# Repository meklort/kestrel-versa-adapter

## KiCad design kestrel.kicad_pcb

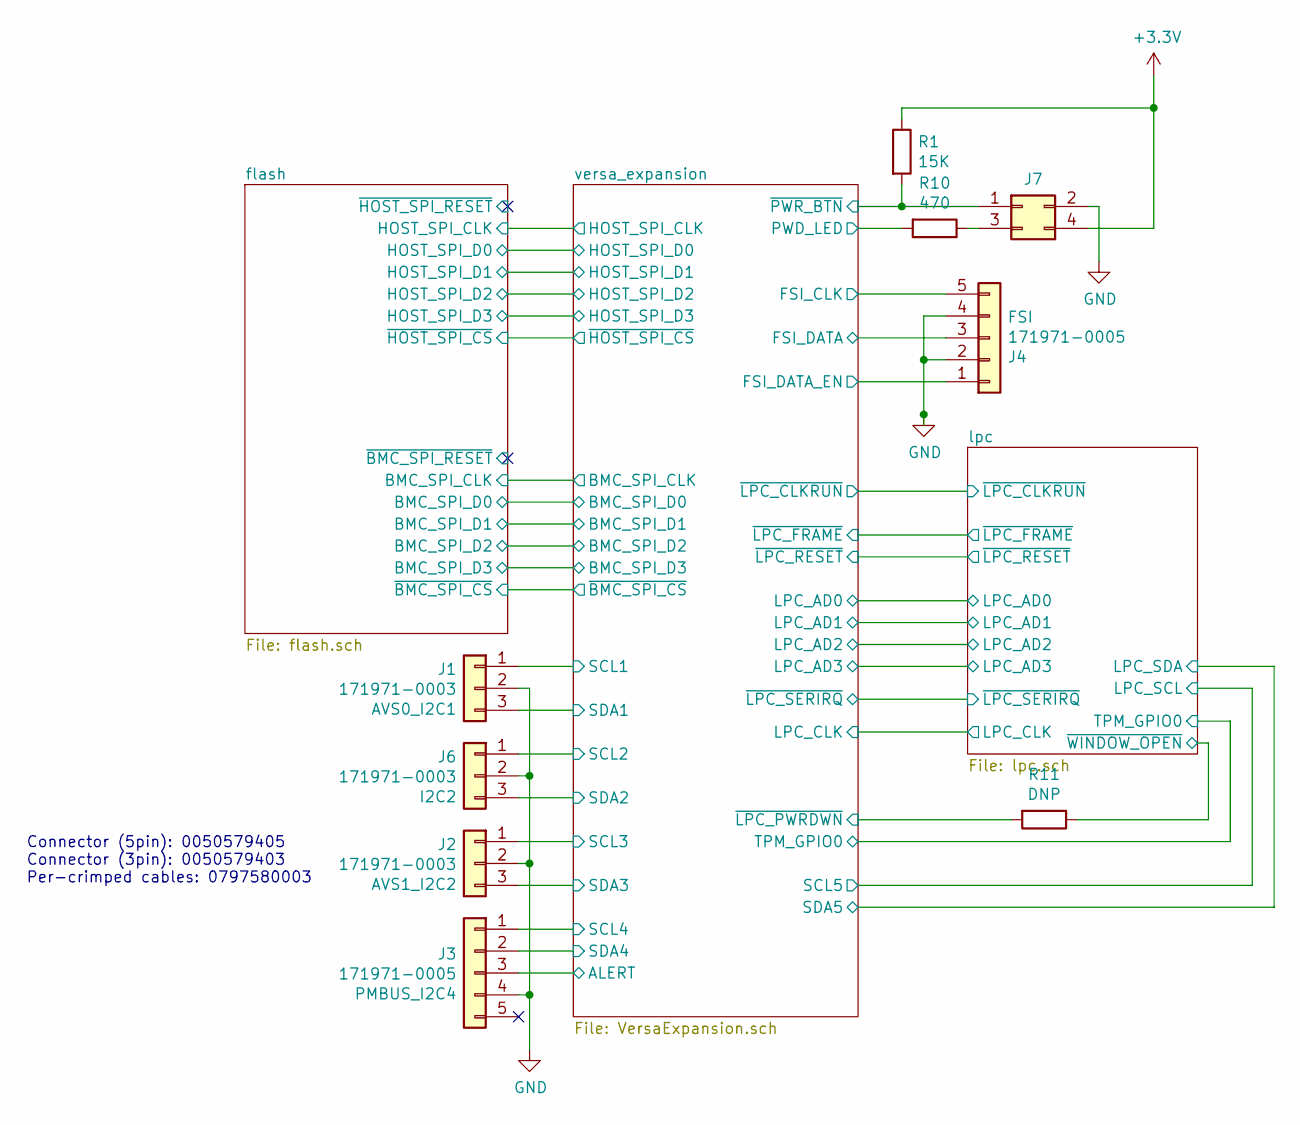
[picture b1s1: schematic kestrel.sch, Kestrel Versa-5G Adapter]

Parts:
J1, J2, J6: 171971-0003; Molex_SL_171971-0003_1x03_P2.54mm_Vertical
J3, J4: 171971-0005; Molex_SL_171971-0005_1x05_P2.54mm_Vertical
J7: Conn_02x02_Odd_Even; PinHeader_2x02_P2.54mm_Vertical
R1: 15K; R_0603_1608Metric_Pad0.98x0.95mm_HandSolder
R10: 470; R_0603_1608Metric_Pad0.98x0.95mm_HandSolder
R11: DNP; R_0603_1608Metric_Pad0.98x0.95mm_HandSolder

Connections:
+3V3: J7.4, R1.1; also elsewhere on the board
/lpc/~WINDOW_OPEN~: R11.1; also elsewhere on the board
/versa_expansion/ALERT: J3.3; also elsewhere on the board
/versa_expansion/FSI_CLK: J4.5; also elsewhere on the board
/versa_expansion/FSI_DATA: J4.3; also elsewhere on the board
/versa_expansion/FSI_DATA_EN: J4.1; also elsewhere on the board
/versa_expansion/PWD_LED: R10.2; also elsewhere on the board
/versa_expansion/SCL1: J1.1; also elsewhere on the board
/versa_expansion/SCL2: J6.1; also elsewhere on the board
/versa_expansion/SCL3: J2.1; also elsewhere on the board
/versa_expansion/SCL4: J3.1; also elsewhere on the board
/versa_expansion/SDA1: J1.3; also elsewhere on the board
/versa_expansion/SDA2: J6.3; also elsewhere on the board
/versa_expansion/SDA3: J2.3; also elsewhere on the board
/versa_expansion/SDA4: J3.2; also elsewhere on the board
/versa_expansion/~LPC_PWRDWN~: R11.2; also elsewhere on the board
/versa_expansion/~PWR_BTN~: J7.1, R1.2; also elsewhere on the board
GND: J1.2, J2.2, J3.4, J4.2, J4.4, J6.2, J7.2; also elsewhere on the board
unnamed: J7.3, R10.1

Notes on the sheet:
Connector (5pin): 0050579405 Connector (3pin): 0050579403 Per-crimped cables: 0797580003

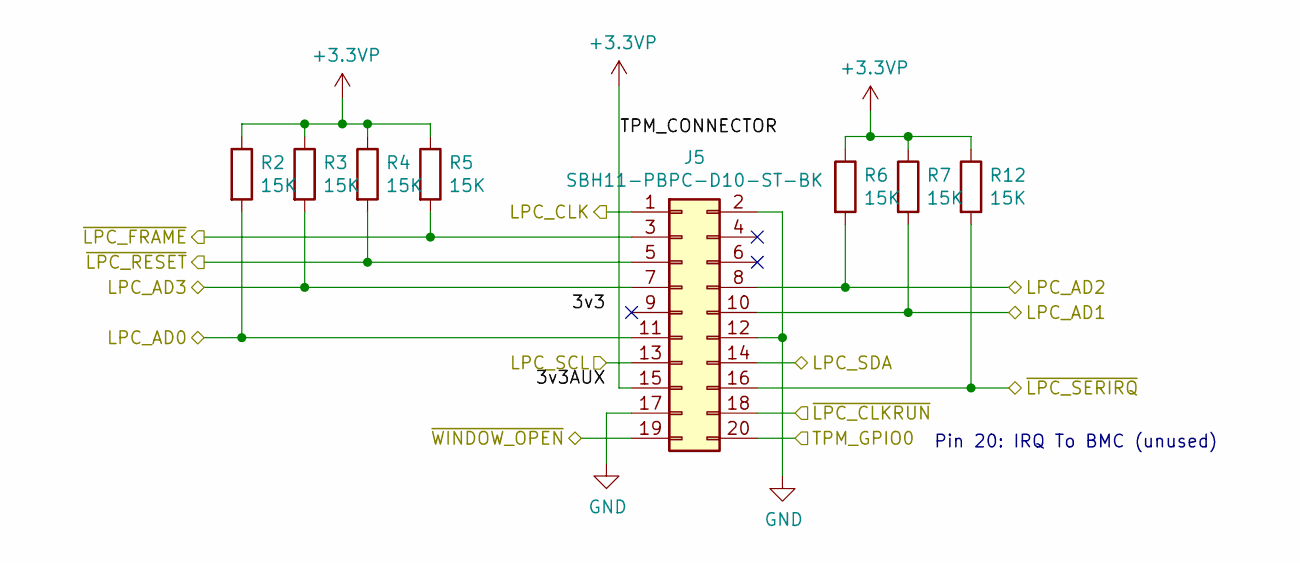
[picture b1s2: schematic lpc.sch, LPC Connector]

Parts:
J5: SBH11-PBPC-D10-ST-BK; PinHeader_2x10_P2.54mm_Vertical
R2, R3, R4, R5, R6, R7, R12: 15K; R_0603_1608Metric_Pad0.98x0.95mm_HandSolder

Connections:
+3.3VP: J5.15, R2.1, R3.1, R4.1, R5.1, R6.1, R7.1, R12.1
/lpc/LPC_AD0: J5.11, R2.2; also elsewhere on the board
/lpc/LPC_AD1: J5.10, R7.2; also elsewhere on the board
/lpc/LPC_AD2: J5.8, R6.2; also elsewhere on the board
/lpc/LPC_AD3: J5.7, R3.2; also elsewhere on the board
/lpc/LPC_CLK: J5.1; also elsewhere on the board
/lpc/LPC_SCL: J5.13; also elsewhere on the board
/lpc/LPC_SDA: J5.14; also elsewhere on the board
/lpc/TPM_GPIO0: J5.20; also elsewhere on the board
/lpc/~LPC_CLKRUN~: J5.18; also elsewhere on the board
/lpc/~LPC_FRAME~: J5.3, R5.2; also elsewhere on the board
/lpc/~LPC_RESET~: J5.5, R4.2; also elsewhere on the board
/lpc/~LPC_SERIRQ~: J5.16, R12.2; also elsewhere on the board
/lpc/~WINDOW_OPEN~: J5.19; also elsewhere on the board
GND: J5.2, J5.12, J5.17; also elsewhere on the board

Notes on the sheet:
Pin 20: IRQ To BMC (unused)

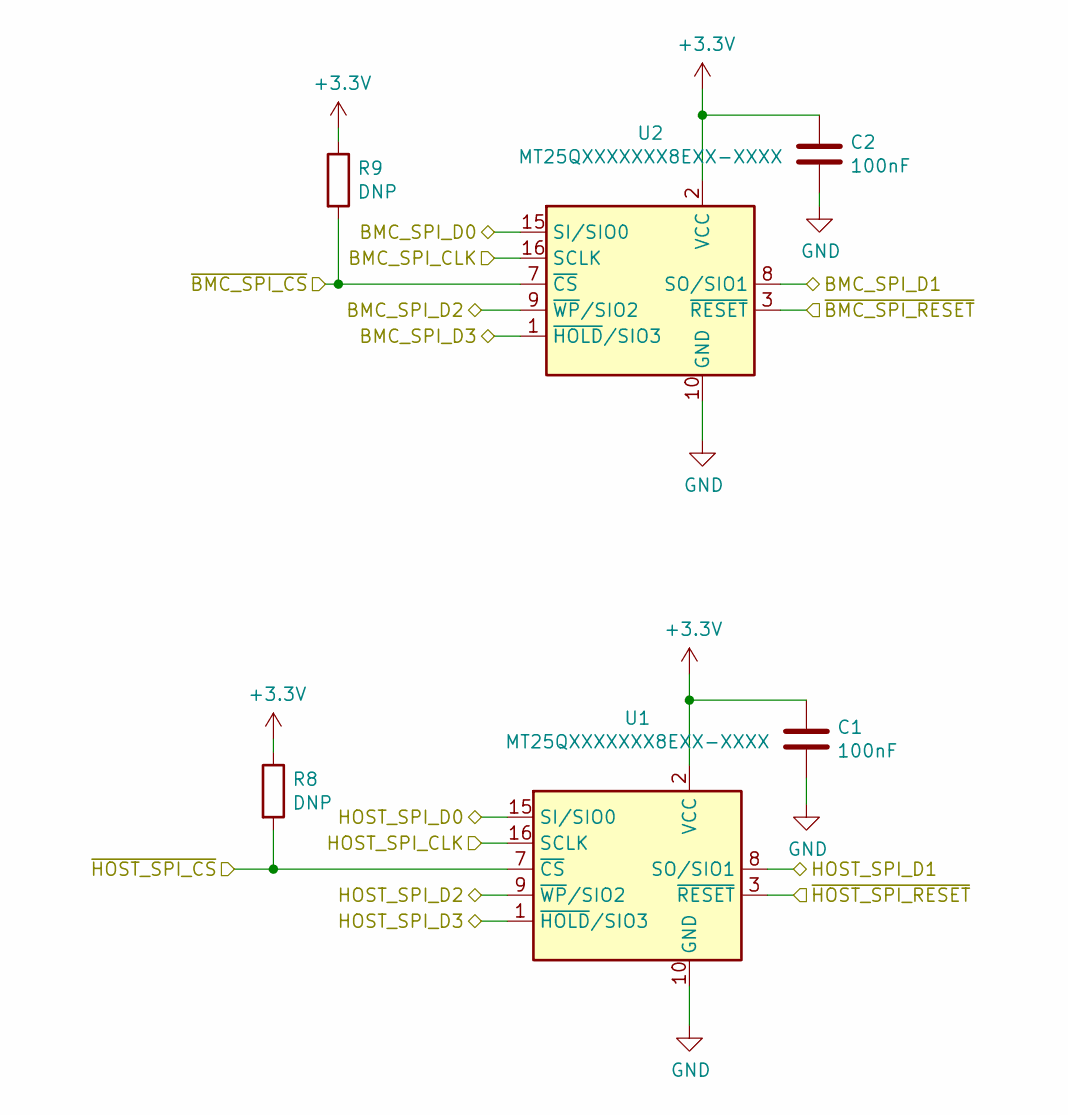
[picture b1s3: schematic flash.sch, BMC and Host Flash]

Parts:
C1, C2: 100nF; C_0603_1608Metric_Pad1.08x0.95mm_HandSolder
R8, R9: DNP; R_0603_1608Metric_Pad0.98x0.95mm_HandSolder
U1, U2: MT25QXXXXXXX8EXX-XXXX; SOIC-16W_7.5x10.3mm_P1.27mm

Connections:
+3V3: C1.1, C2.1, R8.1, R9.1, U1.2 (VCC), U2.2 (VCC); also elsewhere on the board
/flash/BMC_SPI_CLK: U2.16 (SCLK); also elsewhere on the board
/flash/BMC_SPI_D0: U2.15 (SI/SIO0); also elsewhere on the board
/flash/BMC_SPI_D1: U2.8 (SO/SIO1); also elsewhere on the board
/flash/BMC_SPI_D2: U2.9 (~WP~/SIO2); also elsewhere on the board
/flash/BMC_SPI_D3: U2.1 (~HOLD~/SIO3); also elsewhere on the board
/flash/HOST_SPI_CLK: U1.16 (SCLK); also elsewhere on the board
/flash/HOST_SPI_D0: U1.15 (SI/SIO0); also elsewhere on the board
/flash/HOST_SPI_D1: U1.8 (SO/SIO1); also elsewhere on the board
/flash/HOST_SPI_D2: U1.9 (~WP~/SIO2); also elsewhere on the board
/flash/HOST_SPI_D3: U1.1 (~HOLD~/SIO3); also elsewhere on the board
/flash/~BMC_SPI_CS~: R9.2, U2.7 (~CS); also elsewhere on the board
/flash/~BMC_SPI_RESET~: U2.3 (~RESET~)
/flash/~HOST_SPI_CS~: R8.2, U1.7 (~CS); also elsewhere on the board
/flash/~HOST_SPI_RESET~: U1.3 (~RESET~)
GND: C1.2, C2.2, U1.10 (GND), U2.10 (GND); also elsewhere on the board

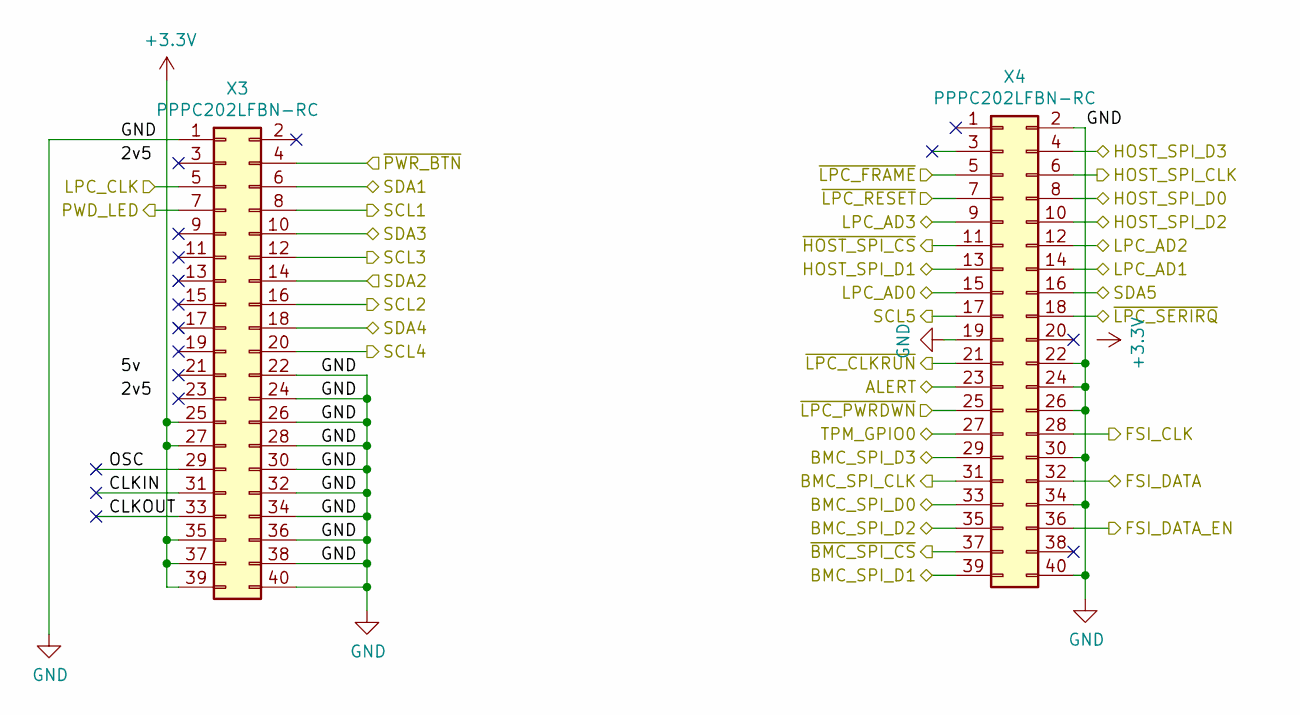
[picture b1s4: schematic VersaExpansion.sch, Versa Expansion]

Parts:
X3, X4: PPPC202LFBN-RC; PinHeader_2x20_P2.54mm_Vertical

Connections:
+3V3: X3.25, X3.27, X3.35, X3.37, X3.39; also elsewhere on the board
/flash/BMC_SPI_CLK: X4.31; also elsewhere on the board
/flash/BMC_SPI_D0: X4.33; also elsewhere on the board
/flash/BMC_SPI_D1: X4.39; also elsewhere on the board
/flash/BMC_SPI_D2: X4.35; also elsewhere on the board
/flash/BMC_SPI_D3: X4.29; also elsewhere on the board
/flash/HOST_SPI_CLK: X4.6; also elsewhere on the board
/flash/HOST_SPI_D0: X4.8; also elsewhere on the board
/flash/HOST_SPI_D1: X4.13; also elsewhere on the board
/flash/HOST_SPI_D2: X4.10; also elsewhere on the board
/flash/HOST_SPI_D3: X4.4; also elsewhere on the board
/flash/~BMC_SPI_CS~: X4.37; also elsewhere on the board
/flash/~HOST_SPI_CS~: X4.11; also elsewhere on the board
/lpc/LPC_AD0: X4.15; also elsewhere on the board
/lpc/LPC_AD1: X4.14; also elsewhere on the board
/lpc/LPC_AD2: X4.12; also elsewhere on the board
/lpc/LPC_AD3: X4.9; also elsewhere on the board
/lpc/LPC_CLK: X3.5; also elsewhere on the board
/lpc/LPC_SCL: X4.17; also elsewhere on the board
/lpc/LPC_SDA: X4.16; also elsewhere on the board
/lpc/TPM_GPIO0: X4.27; also elsewhere on the board
/lpc/~LPC_CLKRUN~: X4.21; also elsewhere on the board
/lpc/~LPC_FRAME~: X4.5; also elsewhere on the board
/lpc/~LPC_RESET~: X4.7; also elsewhere on the board
/lpc/~LPC_SERIRQ~: X4.18; also elsewhere on the board
/versa_expansion/ALERT: X4.23; also elsewhere on the board
/versa_expansion/CLKIN: X3.31
/versa_expansion/CLKOUT: X3.33
/versa_expansion/FSI_CLK: X4.28; also elsewhere on the board
/versa_expansion/FSI_DATA: X4.32; also elsewhere on the board
/versa_expansion/FSI_DATA_EN: X4.36; also elsewhere on the board
/versa_expansion/OSC: X3.29
/versa_expansion/PWD_LED: X3.7; also elsewhere on the board
/versa_expansion/SCL1: X3.8; also elsewhere on the board
/versa_expansion/SCL2: X3.16; also elsewhere on the board
/versa_expansion/SCL3: X3.12; also elsewhere on the board
/versa_expansion/SCL4: X3.20; also elsewhere on the board
/versa_expansion/SDA1: X3.6; also elsewhere on the board
/versa_expansion/SDA2: X3.14; also elsewhere on the board
/versa_expansion/SDA3: X3.10; also elsewhere on the board
/versa_expansion/SDA4: X3.18; also elsewhere on the board
/versa_expansion/~LPC_PWRDWN~: X4.25; also elsewhere on the board
/versa_expansion/~PWR_BTN~: X3.4; also elsewhere on the board
GND: X3.1, X3.22, X3.24, X3.26, X3.28, X3.30, X3.32, X3.34, X3.36, X3.38, X3.40, X4.2, X4.19, X4.22, X4.24, X4.26, X4.30, X4.34, X4.40; also elsewhere on the board

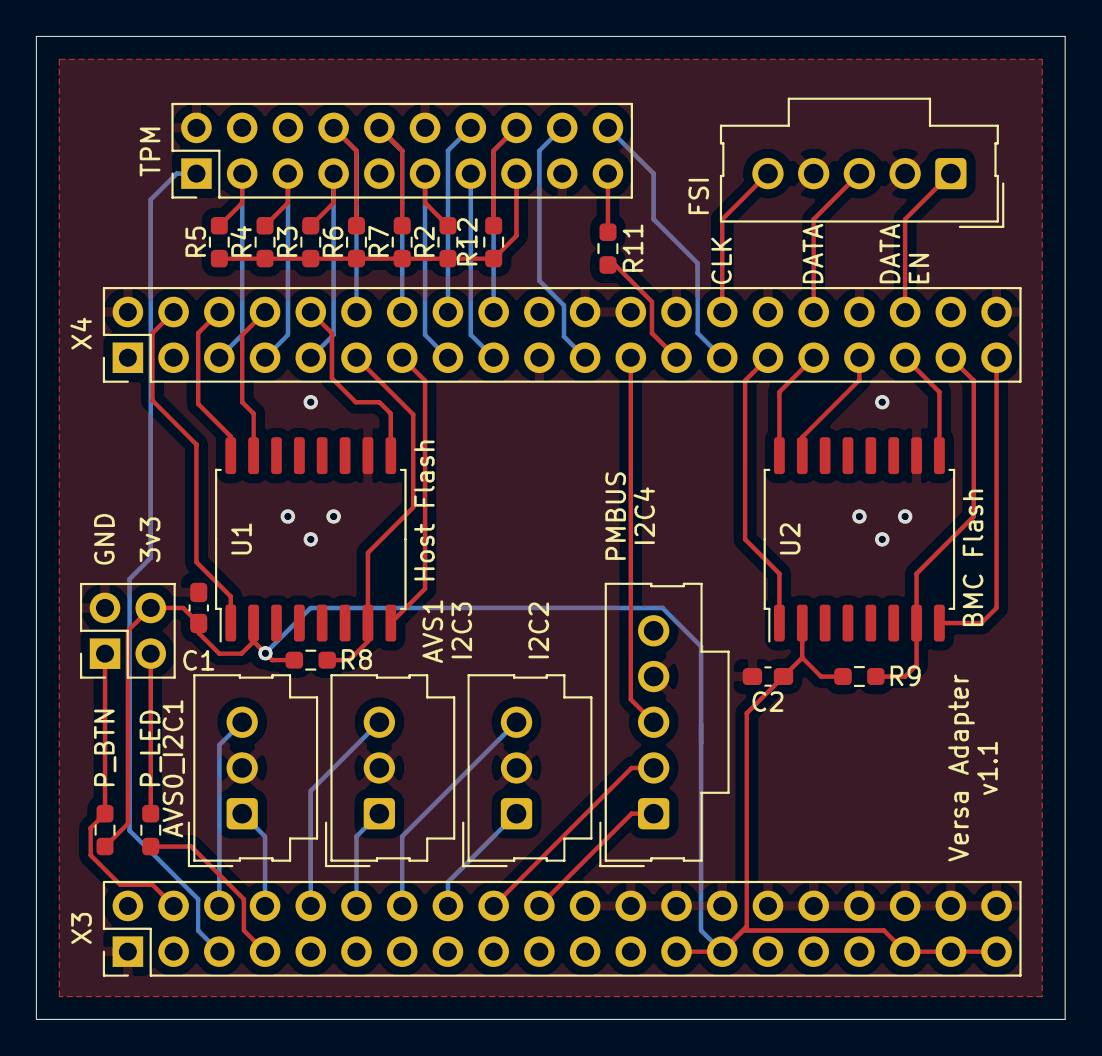
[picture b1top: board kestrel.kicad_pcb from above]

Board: 2 copper layers, 57.2 x 54.6 mm, 25 parts (0 on the bottom side), 44 nets.

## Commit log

2021-02-01 versa-adapter: Initial schematic
2021-02-01 versa-adapter: Fix 3pin connector part number.
2021-02-17 adapter: Update to version 1.1 with minor fixes found during testing.
    - Fix signal naming for host/bmc SPI_CSb and SPI_CLK.
    - Increase distance between FSI and TPM connector to allow for a shrowded TPM connector.
    - Move R8/R9 (unused) to updated Csb signal locations.
    - Fix silk screen for AVS1
2021-04-24 v1.1: Connect LPC_CLK to A12 (was PWR_LED), add pull resistor for SERIRQ.
